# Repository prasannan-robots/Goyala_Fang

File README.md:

# Goyala Fang Robot

A soil-survey robot and its companion app. Mark a field on the map, send the robot a
grid of survey points, and get NPK (nitrogen / phosphorus / potassium) estimates, crop
suggestions and fertilizer advice for every sample.

| Folder | What it is |
| --- | --- |
| `delta/` | **The app ("Saga")** – Flutter, English + Tamil. Current version. |
| `goyalasrm/` | Earlier version of the app (kept for reference). |
| `sketch_mar11a/` | Arduino firmware: SIM800 GSM, drive motors, sampling servo, pH + moisture sensors. |
| `Goyala Fang PCB/` | KiCad PCB design, plus `custom.*` symbols/footprints. |

## How it works

1. **Connect** – in the app, pick SMS (robot's SIM number) or Bluetooth (paired HC-05-style module).
2. **Mark field** – tap the four corners of the field on the satellite map. Drag corners to adjust.
   The app lays a survey grid over the field (density adjustable) as a serpentine path.
3. **Send to robot** – waypoints go out as `GPS: lat,lng; lat,lng; …` messages (each fits one
   SMS), followed by `Start`.
4. **Readings** – the robot replies per sample; the app runs the bundled TFLite model
   (`[pH, EC, moisture] → [N, P, K]`), colours each sample by soil health, and builds a final
   report when the robot sends `D:`.

### Robot → app messages

```
S:Lat:<lat>,Lng:<lng>,Sensor:<pH>-<EC>-<moisture>   sensor reading
C:Lat:<lat>,Lng:<lng>                               robot position
D:                                                  survey finished
```

Bluetooth messages end with `;`. Sensor values may also be separated by commas or spaces.

> **Known gap:** the NPK model needs **pH, EC and moisture**, but the current board only has pH
> and moisture sensors, and sends raw `analogRead()` values with fixed coordinates. The app shows
> those readings but can't predict NPK until an EC sensor (and GPS + calibration) is added.

## Running the app

```sh
cd delta
flutter pub get
flutter test
flutter run
```

Google Maps needs an API key with **Maps SDK for Android** enabled. Put it on its own line in
`delta/android/local.properties` (gitignored — never commit keys):

```
MAPS_API_KEY=your_key_here
```

Restrict the key in Google Cloud Console to the Maps SDK and this app's package name.

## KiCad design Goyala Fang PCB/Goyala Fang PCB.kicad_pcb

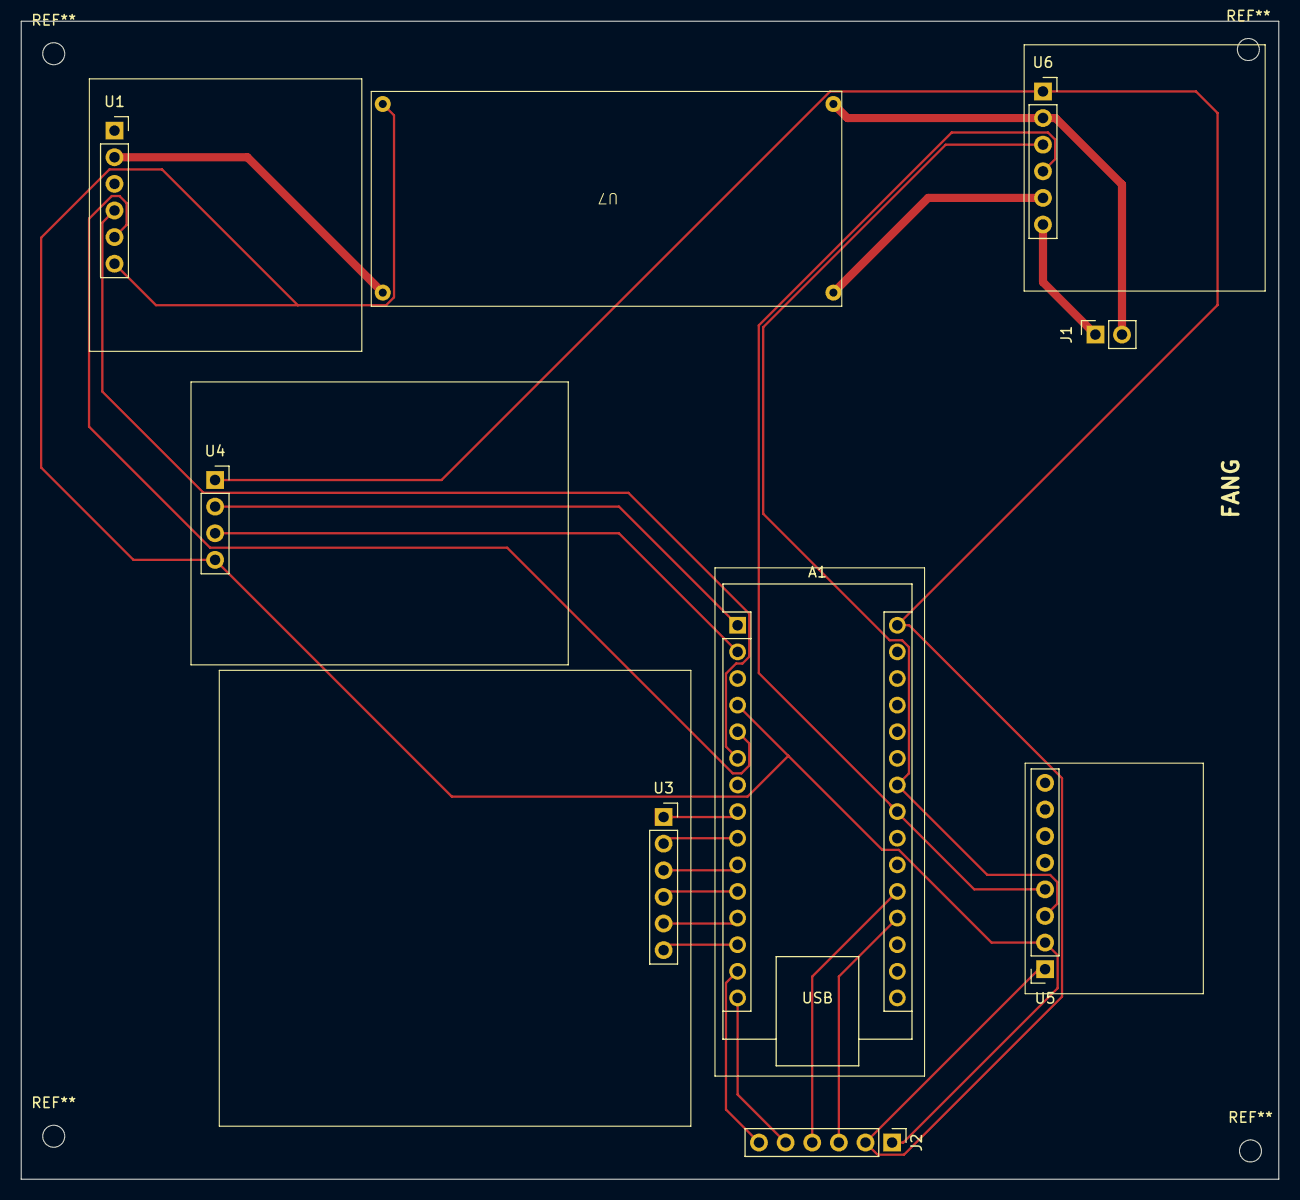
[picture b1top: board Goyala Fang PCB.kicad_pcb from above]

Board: 2 copper layers, 120.0 x 110.5 mm, 9 parts (0 on the bottom side), 21 nets.

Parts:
A1: Arduino_Nano_v3.x; Arduino_Nano
J1: Input Battery; PinSocket_1x02_P2.54mm_Vertical
J2: Conn_01x06; PinHeader_1x06_P2.54mm_Vertical
U1: PinSocket_1x06_P2.54mm_Vertical
U3: L298N; PinSocket_1x06_P2.54mm_Vertical
U4: PinSocket_1x04_P2.54mm_Vertical
U5: MPU-6050; PinSocket_1x08_P2.54mm_Vertical
U6: INA219AxD; PinSocket_1x06_P2.54mm_Vertical
U7: buck

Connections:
+3.3V: U1.2 (Vcc), U7.3 (OUT+)
+5V: A1.30 (VIN), J2.2, U4.1 (Vcc), U5.1 (VDD), U6.1 (VS)
GND: A1.4 (GND), J1.2, J2.1, U1.6 (GND), U4.4 (GND), U5.2 (GND), U6.2 (GND), U7.2 (IN-), U7.4 (OUT-)
unnamed: A1.19 (A0), J2.3 (Pin_5)
unnamed: A1.20 (A1), J2.4
unnamed: A1.2 (D0/RX), U4.3 (Tx)
unnamed: A1.1 (D1/TX), U4.2 (Rx)
unnamed: A1.5 (D2), U1.5 (TXD)
unnamed: A1.6 (D3), U1.4 (RXD)
unnamed: A1.14 (D11), J2.6
unnamed: A1.15 (D12), J2.5 (Pin_3)
unnamed: J1.1, U6.6 (IN+)
unnamed: U6.5 (IN-), U7.1 (IN+)
ena: A1.13 (D10), U3.6 (EnA)
enb: A1.8 (D5), U3.1 (EnB)
in1: A1.12 (D9), U3.5 (IN1)
in2: A1.11 (D8), U3.4 (IN2)
in3: A1.10 (D7), U3.3 (IN3)
in4: A1.9 (D6), U3.2 (IN4)
scl: A1.24 (A5), U5.3 (SCL), U6.3 (SCL)
sda: A1.23 (A4), U5.4 (SDA), U6.4 (SDA)

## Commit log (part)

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2025-02-13 [Feat] Start
2025-02-13 [Fix] Added PCB Footprints
2025-02-26 [Feat] Added App
2025-03-12 Upddate
2025-03-20 delata
2025-03-20 [Fix] Added BLE
